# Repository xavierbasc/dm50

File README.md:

# DM50 calculator

The main features of the calculator are the following:

 - 32bit ARM Cortex-M33 MCU ultra low power.
 - Mathematical coprocessor acceleration.
 - Floating Point Unit (FPU).
 - 2MB RAM (STM32U595RJ).
 - 4MB FLASH memory (STM32U595RJ).
 - 16MB FLASH storage Octo-SPI (accessible via USB).
 - USBC port, connects as USB mass storage device.
 - Serial port for communications with external devices.
 - MicroSD memory slot.
 - Integrated speaker and stereo audio output (jack 3.5).
 - Graphic LCD Display (128x64 dots).
 - ESD protection of USBC.
 - LiPO 3.7V rechargeable battery, with JST PH2.0 connector.
 - Possibility of using AAA batteries.
 - Battery charge level sensor.
 - USB power and battery charging status LED indicators.
 - JTAG debug port.
 - Temperature sensor.
 - Same number of keys as the legendary HP48.

# Hardware
Below is a list of the most relevant electronic components:

1. Processor: STM32U5 ARM Cortex-M33 ultra low power with FPU.
2. Display: EA_DOGL128L-6 STN reflective display 128x64.
3. Flash memory: W25Q128JVSIQ 16MB Flash.
4. Voltage regulator: ADP2108 Vin 2.3 - 5.5, Vout 3.3.
5. USB protection: USBLC6-2 ESD protection of VBUS.
6. Battery charger: MCP73831 Lithium-Ion/Lithium-Polymer Battery Charger.

Some of the supported batteries are as follows:

| Batteries | Capacity (mha) |
| --- | :---: |
| AAA Alkaline | 900 - 1155 |
| AAA Ni-MH | 800 - 1000 |
| LiPO 402025 (4.0x20x25) | 150 |
| LiPO LP272247 (2.7x22x47) | 260 |

***Electronic design***:

## Case
Freecad software has been used to design the casing.
The spaces have been optimized to reduce the size, continuously giving shape to the calculator and improving the user experience.

## Faceplate
A master faceplate has been designed although it can be exchanged by the user through a simple manual process.

The front plate is printed on photographic paper and cut to size, with professional results. A photo-quality printer is recommended, such as the Epson Ecotank.

To create the faceplate, the Inkscape tool has been used to edit the SVG and the font used is Latin Modern Math, licensed by the GUST Font License, developed by the TeX user group in Poland, and can be used for academic use. , commercial or academic.

[Latin Modern Math font](https://www.gust.org.pl/projects/e-foundry/latin-modern "Latin Modern Math font")

# Software
TBD

# Reference
Comparison of the ***hardware*** used in the different reference calculators:

| Year | Model | Processor | FREQ | RAM | FLASH | Display | MIPS |
| :-: | - | - | -: | -: | -: | :-: | -: |
| 1988 | [HP42S](https://en.wikipedia.org/wiki/HP-42S) | HP Saturn (1LF5) | - | 8KB | 64KB | 131×16 | 0.5 |
| 1993 | [HP48G](https://en.wikipedia.org/wiki/HP_48_series) | HP Saturn (1LF2) | 4MHz | 32KB | 512KB | 131×64 | 0.5 |
| 2006 | [HP50G](https://en.wikipedia.org/wiki/HP_49/50_series) | ARM9 S3C2410 | 75MHz | 512KB | 2MB | 131×80 | 75 |
| 2013 | [TI-Nspire CX II](https://en.wikipedia.org/wiki/TI-Nspire_series#TI-Nspire_CX_II_and_TI-Nspire_CX_II_CAS) | TI OMAP 3530 | 396MHz | 64MB | 128MB | 320x240 | 792 |
| 2016 | [NumWorks](https://www.numworks.com/resources/engineering/hardware/) | STM32F730V8T6 | 216MHz | 256KB | 6MB | 320x240 | 432 |
| 2017 | [DM42](https://www.swissmicros.com/product/dm42) | STM32L476RG | 80MHz | 128KB | 6MB | 400×240 |  100 |
| 2019 | [HP Prime G2](https://en.wikipedia.org/wiki/HP_Prime) | i. MX 6ULL | 528MHz | 256MB | 512MB | 320×240 | 1710 |
| 2021 | [OpenRPNCalc](https://github.com/apoluekt/OpenRPNCalc) | STM32L476 | 8MHz | 128KB | 1MB | 400x240 | 100 |
| 2023 | [DM32](https://www.swissmicros.com/product/dm42) | STM32U575 | 160MHz | 786KB | 1MB | 400×240 |  240 |
| 2024 | [`DM50`](https://github.com/xavierbasc/dm50-calculator) | STM32U595RJ | 160MHz | 2MB | 20MB | 128×64 | 240 |

List of ***software*** used as firmware in some calculators:

1. [DB48X](https://48calc.org/): DB48X is a modern implementation of RPL.
2. [C47](https://47calc.com/): C47 is a RPN Scientific Calculator (old WP43C project).
3. [WP43](https://gitlab.com/rpncalculators/wp43): Firmware for the WP43 pocket calculator (old WP43S project).
4. [Free42](https://github.com/thomasokken/free42): Free42 is a software clone of the Hewlett-Packard 42S calculator.
5. [TCalc](https://github.com/tylertian123/TCalc): Firmware for STM32 CAS calculator.
6. [TinyExpr](https://github.com/codeplea/tinyexpr): parser and evaluation for math expressions.
7. [Giac](https://www-fourier.ujf-grenoble.fr/~parisse/giac.html): CAS calculation engine used in HP Prime, Casio Graph 90, Casio 35eii, TI Nspire CX, Numworks, and software such as Geogebra and PocketCAS.

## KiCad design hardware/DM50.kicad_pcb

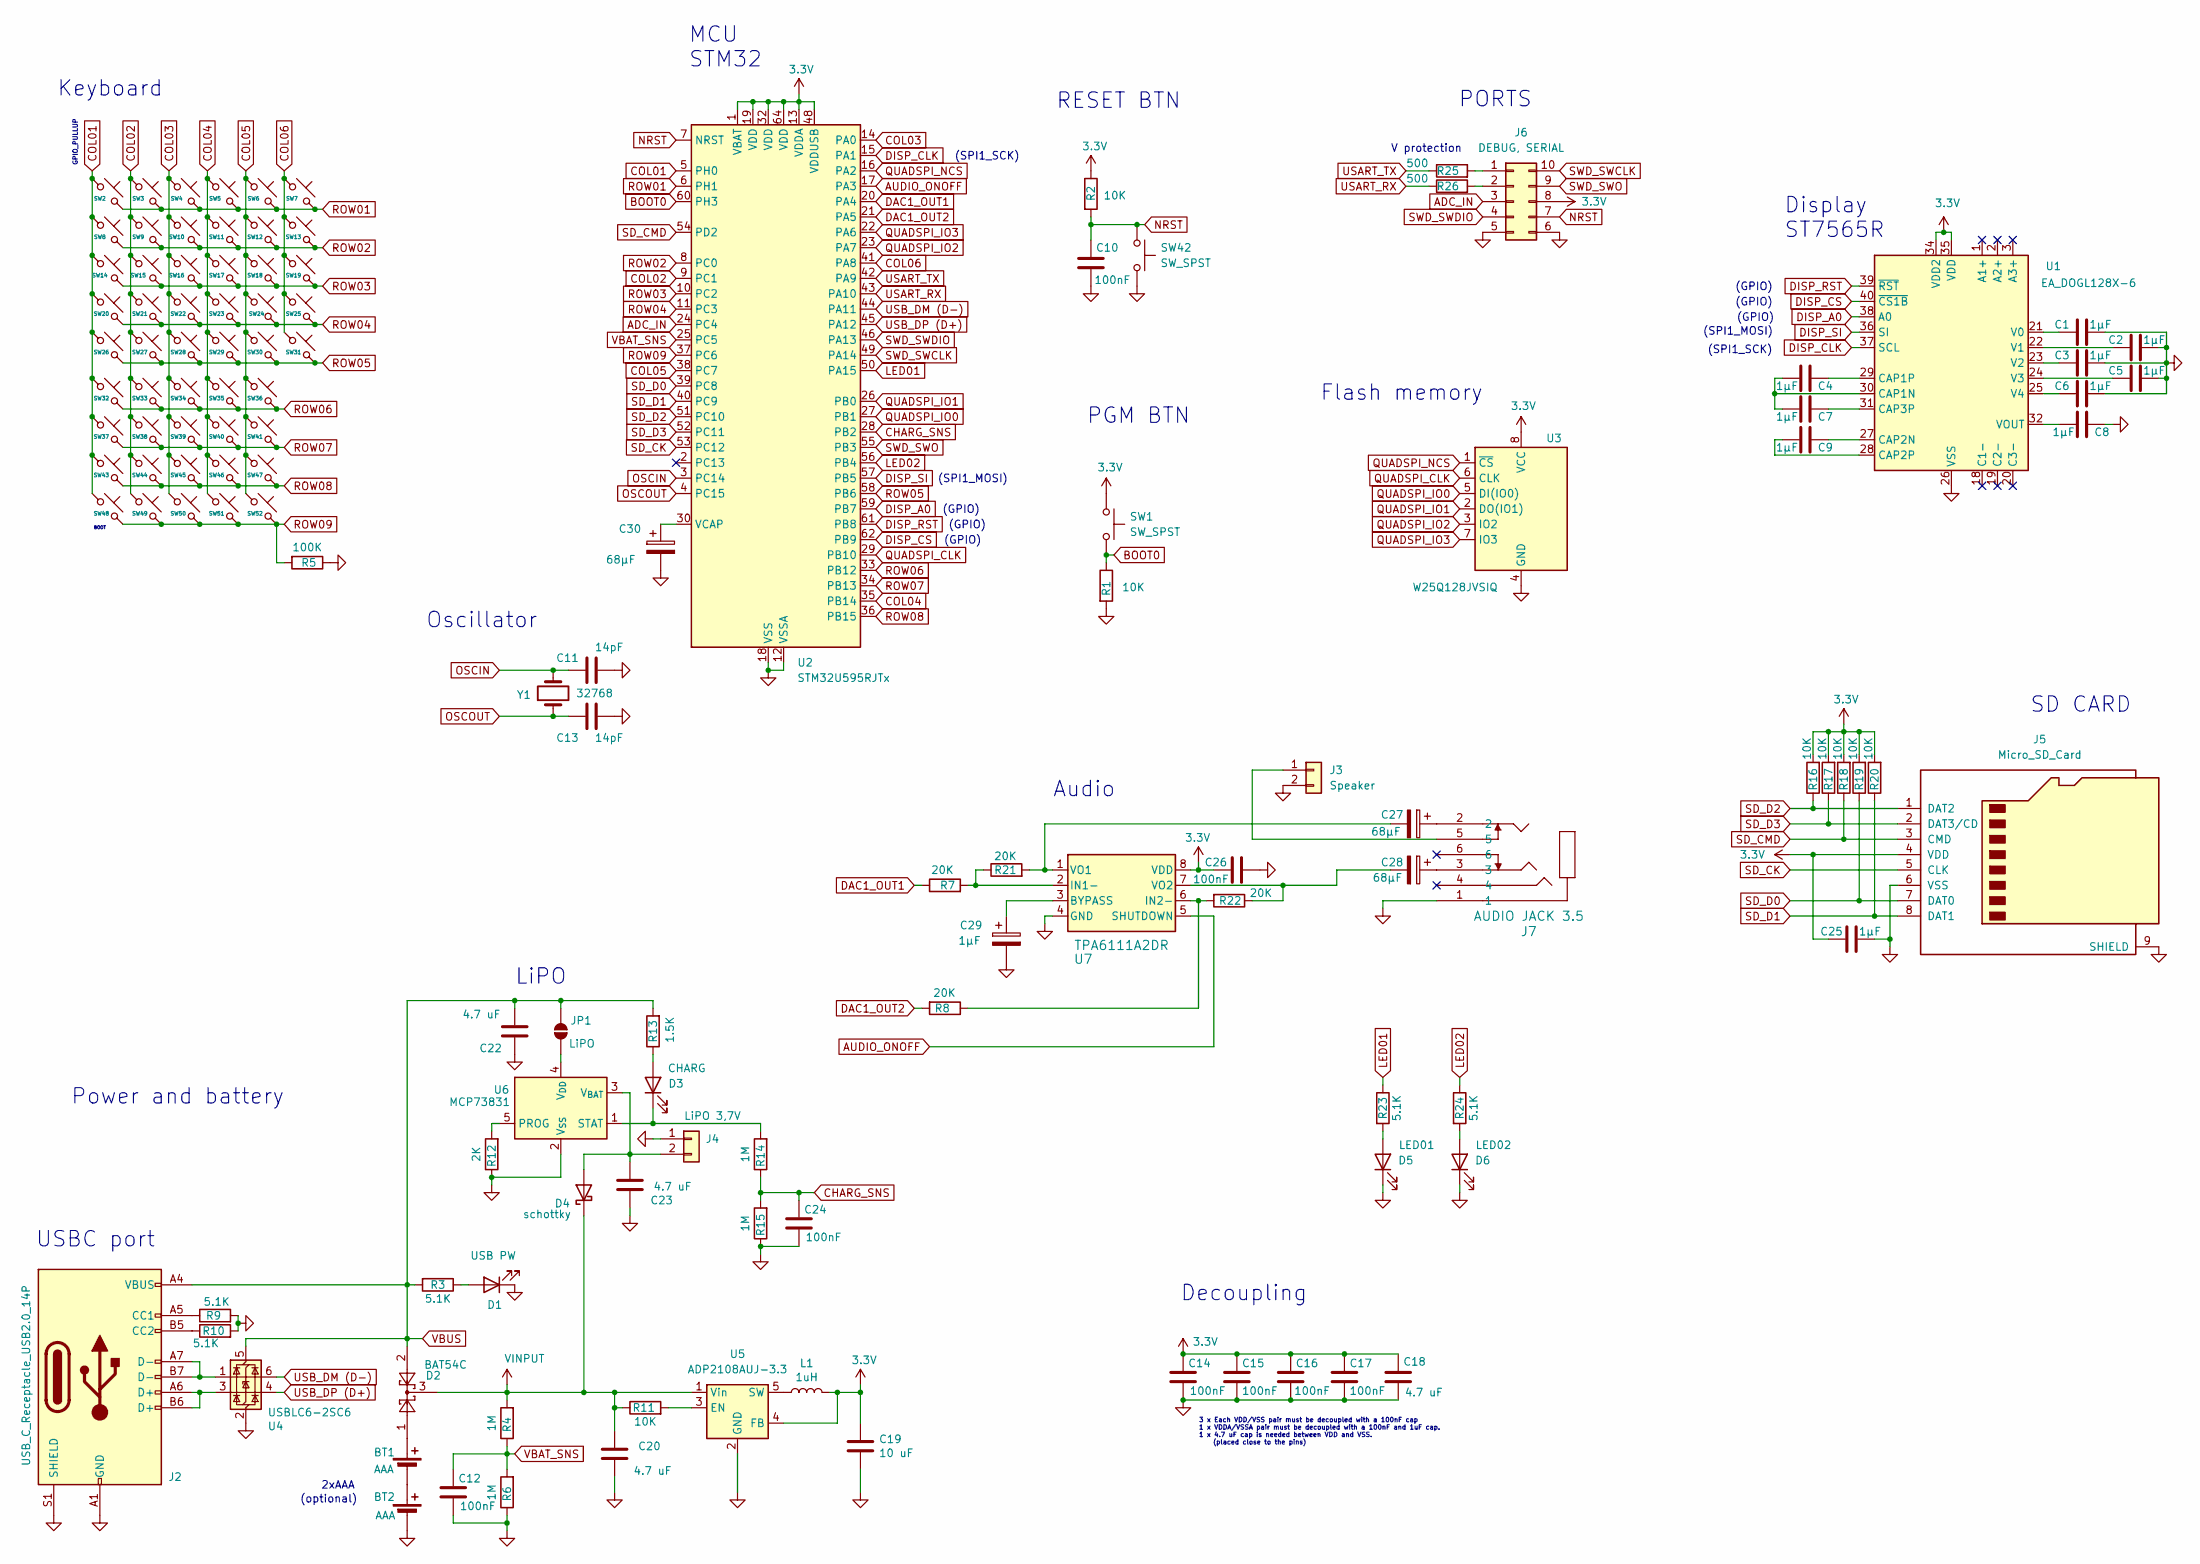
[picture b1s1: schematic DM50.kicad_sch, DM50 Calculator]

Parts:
BT1, BT2: AAA; dm50-batAAA; Digikey BK-82 (x4)
C1, C2, C3, C4, C5, C6, C7, C8, C9, C25, C29: 1µF; C_0603_1608Metric; Digikey CC0603KRX7R7BB105
C10, C12, C14, C15, C16, C17, C24, C26: 100nF; C_0603_1608Metric; Digikey CC0603KRX7R7BB104
C11, C13: 14pF; C_0603_1608Metric; Digikey CL10C060DB8NNNC
C18, C20, C22, C23: 4.7 uF; C_0603_1608Metric; Digikey CL10A475KP8NNNC
C19: 10 uF; C_0603_1608Metric; Digikey LMK107BBJ106MALT
C27, C28, C30: 68µF; C_1210_3225Metric; Digikey C3216X5R0J686M160AB
D1: USB PW; LED_0603_1608Metric; Digikey LTST-C190GKT
D2: BAT54C; SOT-23; Digikey BAT54C
D3: CHARG; LED_0603_1608Metric; Digikey LTST-S270KRKT
D4: schottky; D_SOD-323; Digikey 1PS76SB10,115
D5: LED01; LED_0603_1608Metric; Digikey LTST-S270KRKT
D6: LED02; LED_0603_1608Metric; Digikey LTST-S270KRKT
J2: USB_C_Receptacle_USB2.0_14P; USB_C_Receptacle_GCT_USB4105-xx-A_16P_TopMnt_Horizontal; Digikey 12402012E212A
J3: Speaker; Buzzer; Digikey CMS-15113-078L100
J4: LiPO 3,7V; CONN_S2B-PH-K-S_JST; Digikey S2B-PH-K-S
J5: Micro_SD_Card; 502570-0893_MOL; Digikey DM3AT-SF-PEJM5
J6: DEBUG, SERIAL; 610110249221; Digikey 610110249221
J7: AUDIO JACK 3.5; SJ-43516-SMT_CUD; Digikey SJ-43516-SMT-TR
JP1: LiPO; SolderJumper-2_P1.3mm_Bridged_RoundedPad1.0x1.5mm
L1: 1uH; L_0805_2012Metric_Pad1.15x1.40mm_HandSolder; Digikey MLZ1608A1R0WT000
R1, R2, R11, R16, R17, R18, R19, R20: 10K; R_0603_1608Metric; Digikey RMCF0603JT10K0
R3, R9, R10, R23, R24: 5.1K; R_0603_1608Metric; Digikey RC0603FR-075K1L
R4, R6, R14, R15: 1M; R_0603_1608Metric; Digikey RMCF0603FT1M00
R5: 100K; R_0603_1608Metric; Digikey RC0603FR-07100KL
R7, R8, R21, R22: 20K; R_0603_1608Metric; Digikey RMCF0603JT10K0
R12: 2K; R_0603_1608Metric; Digikey ERJ-3EKF2001V
R13: 1.5K; R_0603_1608Metric; Digikey RC0603JR-071K5L
R25, R26: 500; R_0603_1608Metric; Digikey RMCF0603JT10K0
SW1, SW42: SW_SPST; SW_SPST_CK_KMS2xxG; Digikey KMS223GPLFG
SW2, SW3, SW4, SW5, SW6, SW7, SW8, SW9, SW10, SW11, SW12, SW13, SW14, SW15, SW16, SW17, SW18, SW19, SW20, SW21, SW22, SW23, SW24, SW25, SW26, SW27, SW28, SW29, SW30, SW31, SW32, SW33, SW34, SW35, SW36, SW37, SW38, SW39, SW40, SW41, SW43, SW44, SW45, SW46, SW47, SW48, SW49, SW50, SW51, SW52: BT_SMD; dm50-button; Digikey dome 7.0mm, three dimple
U1: EA_DOGL128X-6; EA DOGL128L-6; Digikey EA DOGL128L-6
U2: STM32U595RJTx; LQFP-64_10x10mm_P0.5mm; Digikey STM32U595RJTx
U3: W25Q128JVSIQ; SOIC-8_3.9x4.9mm_P1.27mm; Digikey W25Q128JVSIQ
U4: USBLC6-2SC6; SOT-23-6; Digikey USBLC6-2SC6
U5: ADP2108AUJ-3.3; TSOT-23-5; Digikey ADP2108AUJZ-3.3-R7
U6: MCP73831; SOT-23-5; Digikey MCP73831T-2ACI/OT
U7: TPA6111A2DR; SOIC-8-1EP_3.9x4.9mm_P1.27mm_EP2.41x3.81mm_ThermalVias; Digikey TPA6111A2DR
Y1: 32768; XTAL_ABS05-32.768KHZ-9-T

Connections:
3.3V: C14.1, C15.1, C16.1, C17.1, C18.1, C19.1, C25.1, C26.1, J5.4 (VDD), J6.8, L1.2, R2.1, R16.2, R17.2, R18.2, R19.2, R20.2, SW1.1, U1.34 (VDD2), U1.35 (VDD), U2.1 (VBAT), U2.13 (VDDA), U2.19 (VDD), U2.32 (VDD), U2.48 (VDDUSB), U2.64 (VDD), U3.8 (VCC), U5.4 (FB), U7.8 (VDD)
ADC_IN: J6.3, U2.24 (PC4)
AUDIO_ONOFF: U2.17 (PA3), U7.5 (SHUTDOWN)
BOOT0: R1.1, SW1.2, U2.60 (PH3)
CHARG_SNS: C24.1, R14.1, R15.2, U2.28 (PB2)
COL01: SW2.1, SW8.1, SW14.1, SW20.1, SW26.1, SW32.1, SW37.1, SW43.1, SW48.1, U2.5 (PH0)
COL02: SW3.1, SW9.1, SW15.1, SW21.1, SW27.1, SW33.1, SW38.1, SW44.1, SW49.1, U2.9 (PC1)
COL03: SW4.1, SW10.1, SW16.1, SW22.1, SW28.1, SW34.1, SW39.1, SW45.1, SW50.1, U2.14 (PA0)
COL04: SW5.1, SW11.1, SW17.1, SW23.1, SW29.1, SW35.1, SW40.1, SW46.1, SW51.1, U2.35 (PB14)
COL05: SW6.1, SW12.1, SW18.1, SW24.1, SW30.1, SW36.1, SW41.1, SW47.1, SW52.1, U2.38 (PC7)
COL06: SW7.1, SW13.1, SW19.1, SW25.1, SW31.1, U2.41 (PA8)
DAC1_OUT1: R7.1, U2.20 (PA4)
DAC1_OUT2: R8.2, U2.21 (PA5)
DISP_A0: U1.38 (A0), U2.59 (PB7)
DISP_CLK: U1.37 (SCL), U2.15 (PA1)
DISP_CS: U1.40 (~CS1B), U2.62 (PB9)
DISP_RST: U1.39 (~RST), U2.61 (PB8)
DISP_SI: U1.36 (SI), U2.57 (PB5)
GND: BT2.2 (-), C1.2, C2.2, C3.2, C5.2, C6.2, C8.1, C10.2, C11.2, C12.2, C13.2, C14.2, C15.2, C16.2, C17.2, C18.2, C19.2, C20.2, C22.1, C23.2, C24.2, C25.2, C26.2, C29.2, C30.2, D1.1 (K), D5.1 (K), D6.1 (K), J2.A1 (GND), J2.A12 (GND), J2.B1 (GND), J2.B12 (GND), J2.S1 (SHIELD), J3.2, J4.1, J5.6 (VSS), J5.9 (SHIELD), J6.5, J6.6, J7.1, R1.2, R5.1, R6.1, R9.2, R10.2, R12.1, R15.1, SW42.2, U1.26 (VSS), U1.33 (VSS), U2.12 (VSSA), U2.18 (VSS), U2.31 (VSS), U2.47 (VSS), U2.63 (VSS), U3.4 (GND), U4.2 (GND), U5.2 (GND), U6.2 (V_{SS}), U7.4 (GND)
LED01: R23.1, U2.50 (PA15)
LED02: R24.1, U2.56 (PB4)
NRST: C10.1, J6.7, R2.2, SW42.1, U2.7 (NRST)
unnamed: BT1.1 (+), D2.1
unnamed: BT1.2 (-), BT2.1 (+)
unnamed: C27.1, J7.2
unnamed: C28.1, J7.3
unnamed: D1.2 (A), R3.1
unnamed: D3.2 (A), R13.1
unnamed: D3.1 (K), R14.2, U6.1 (STAT)
unnamed: C23.1, D4.2 (A), J4.2, U6.3 (V_{BAT})
unnamed: D5.2 (A), R23.2
unnamed: D6.2 (A), R24.2
unnamed: J2.A5 (CC1), R9.1
unnamed: J2.B5 (CC2), R10.1
unnamed: J2.A6 (D+), J2.B6 (D+), U4.3 (I/O2)
unnamed: J2.A7 (D-), J2.B7 (D-), U4.1 (I/O1)
unnamed: J3.1, J7.5
unnamed: J6.1, R25.2
unnamed: J6.2, R26.2
unnamed: JP1.1 (A), U6.4 (V_{DD})
unnamed: C4.2, C7.2, U1.30 (CAP1N)
unnamed: C4.1, U1.29 (CAP1P)
unnamed: C9.1, U1.27 (CAP2N)
unnamed: C9.2, U1.28 (CAP2P)
unnamed: C7.1, U1.31 (CAP3P)
unnamed: C1.1, U1.21 (V0)
unnamed: C2.1, U1.22 (V1)
unnamed: C3.1, U1.23 (V2)
unnamed: C5.1, U1.24 (V3)
unnamed: C6.1, U1.25 (V4)
unnamed: C8.2, U1.32 (VOUT)
unnamed: C30.1, U2.30 (VCAP)
unnamed: R11.2, U5.3 (EN)
unnamed: L1.1, U5.5 (SW)
unnamed: R12.2, U6.5 (PROG)
unnamed: C29.1, U7.3 (BYPASS)
unnamed: R7.2, R21.1, U7.2 (IN1-)
unnamed: R8.1, R22.2, U7.6 (IN2-)
unnamed: C27.2, R21.2, U7.1 (VO1)
unnamed: C28.2, R22.1, U7.7 (VO2)
OSCIN: C11.1, U2.3 (PC14), Y1.2
OSCOUT: C13.1, U2.4 (PC15), Y1.1
QUADSPI_CLK: U2.29 (PB10), U3.6 (CLK)
QUADSPI_IO0: U2.27 (PB1), U3.5 (DI(IO0))
QUADSPI_IO1: U2.26 (PB0), U3.2 (DO(IO1))
QUADSPI_IO2: U2.23 (PA7), U3.3 (IO2)
QUADSPI_IO3: U2.22 (PA6), U3.7 (IO3)
QUADSPI_NCS: U2.16 (PA2), U3.1 (~CS)
ROW01: SW2.2, SW3.2, SW4.2, SW5.2, SW6.2, SW7.2, U2.6 (PH1)
ROW02: SW8.2, SW9.2, SW10.2, SW11.2, SW12.2, SW13.2, U2.8 (PC0)
ROW03: SW14.2, SW15.2, SW16.2, SW17.2, SW18.2, SW19.2, U2.10 (PC2)
ROW04: SW20.2, SW21.2, SW22.2, SW23.2, SW24.2, SW25.2, U2.11 (PC3)
ROW05: SW26.2, SW27.2, SW28.2, SW29.2, SW30.2, SW31.2, U2.58 (PB6)
ROW06: SW32.2, SW33.2, SW34.2, SW35.2, SW36.2, U2.33 (PB12)
ROW07: SW37.2, SW38.2, SW39.2, SW40.2, SW41.2, U2.34 (PB13)
ROW08: SW43.2, SW44.2, SW45.2, SW46.2, SW47.2, U2.36 (PB15)
ROW09: R5.2, SW48.2, SW49.2, SW50.2, SW51.2, SW52.2, U2.37 (PC6)
SD_CK: J5.5 (CLK), U2.53 (PC12)
SD_CMD: J5.3 (CMD), R18.1, U2.54 (PD2)
SD_D0: J5.7 (DAT0), R19.1, U2.39 (PC8)
SD_D1: J5.8 (DAT1), R20.1, U2.40 (PC9)
SD_D2: J5.1 (DAT2), R16.1, U2.51 (PC10)
SD_D3: J5.2 (DAT3/CD), R17.1, U2.52 (PC11)
SWD_SWCLK: J6.10, U2.49 (PA14)
SWD_SWDIO: J6.4, U2.46 (PA13)
SWD_SWO: J6.9, U2.55 (PB3)
USART_RX: R26.1, U2.43 (PA10)
USART_TX: R25.1, U2.42 (PA9)
USB_DM (D-): U2.44 (PA11), U4.6 (I/O1)
USB_DP (D+): U2.45 (PA12), U4.4 (I/O2)
VBAT_SNS: C12.1, R4.1, R6.2, U2.25 (PC5)
VBUS: C22.2, D2.2, J2.A4 (VBUS), J2.A9 (VBUS), J2.B4 (VBUS), J2.B9 (VBUS), JP1.2 (B), R3.2, R13.2, U4.5 (VBUS)
VINPUT: C20.1, D2.3, D4.1 (K), R4.2, R11.1, U5.1 (Vin)

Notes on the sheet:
(GPIO)
Oscillator
(optional)
Decoupling
(SPI1_MOSI)
PORTS
Power and battery
MCU STM32
USBC port
V protection
Keyboard
GPIO_PULLUP
Flash memory
2xAAA
LiPO
Display ST7565R
(SPI1_SCK)
PGM BTN
SD CARD
RESET BTN
3 x Each VDD/VSS pair must be decoupled with a 100nF cap 1 x VDDA/VSSA pair must be decoupled with a 100nF and 1uF cap. 1 x 4.7 uF cap is needed between VDD and VSS. (placed close to the pins)
Audio
BOOT

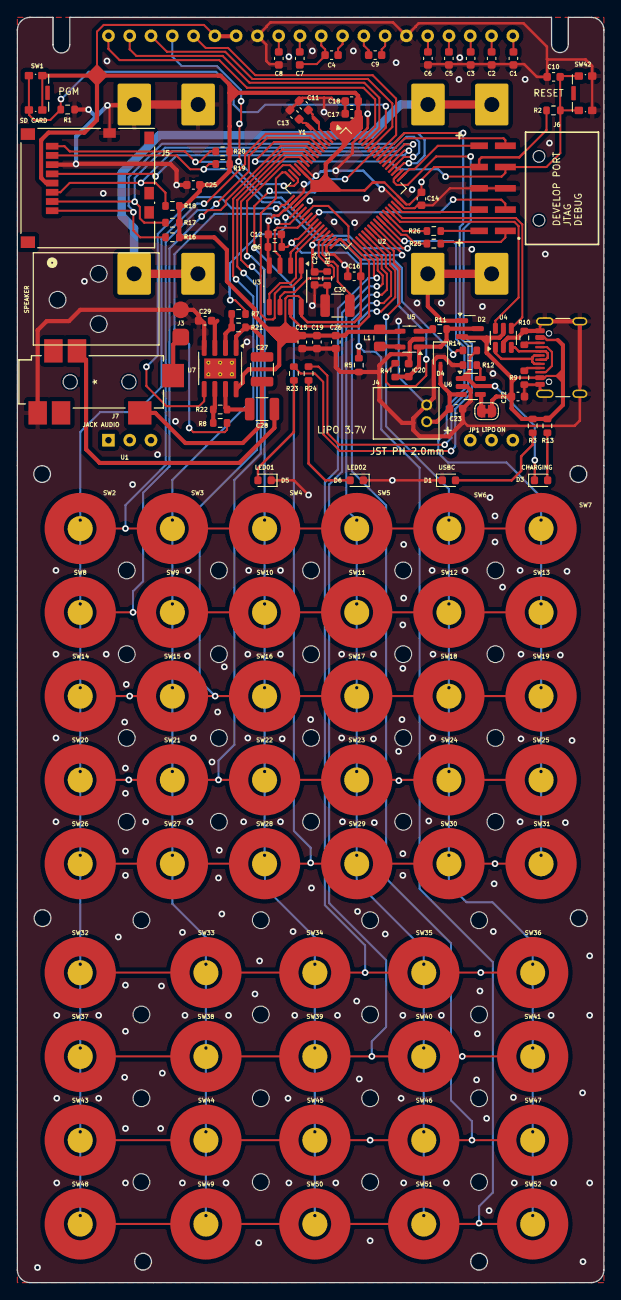
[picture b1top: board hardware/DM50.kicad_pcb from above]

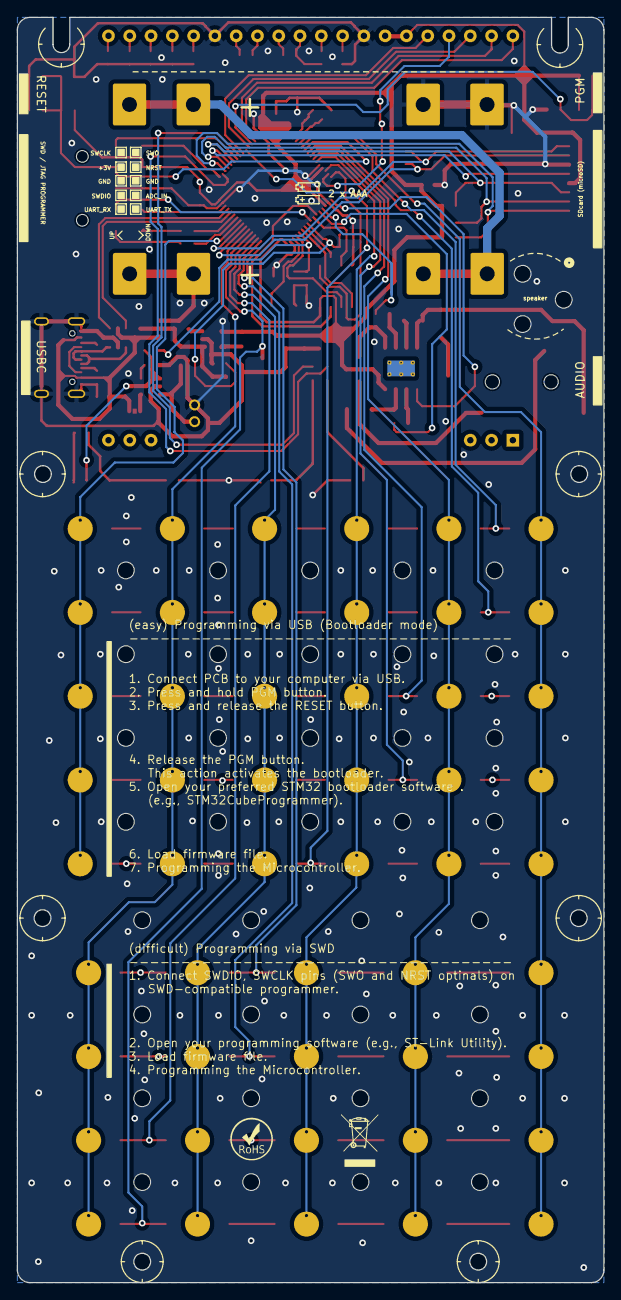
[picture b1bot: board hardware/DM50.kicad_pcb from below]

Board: 2 copper layers, 70.0 x 151.0 mm, 131 parts (2 on the bottom side), 93 nets.

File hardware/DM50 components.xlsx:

Reference | Value | Datasheet | Footprint | Qty | Digikey | Package | Price € | TOTAL | Function |  | BASIC (AAA) | PRO (LiPO+microSD)
C1,C2,C3,C4,C5,C6,C7,C8,C9,C25 | 1uF | https://www.digikey.es/en/products/detail/yageo/CC0603KRX7R7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 | Capacitor_SMD:C_0603_1608Metric | 10 | CC0603KRX7R7BB105 | 0603 | 0.09 | 0.89999999999999991 | Core | UNION 1uF (A8) | 0.89999999999999991 | 0.89999999999999991
C10,C12,C14,C15,C16,C17,C24,C26 | 100nF | https://www.digikey.es/es/products/detail/yageo/CC0603KRX7R7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 | Capacitor_SMD:C_0603_1608Metric | 8 | CC0603KRX7R7BB104 | 0603 | 0.09 | 0.72 | Core |  | 0.72 | 0.72
C11,C13 | 6pF | https://www.digikey.es/es/products/detail/samsung-electro-me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 | Capacitor_SMD:C_0603_1608Metric | 2 | CL10C060DB8NNNC | 0603 | 0.09 | 0.18 | Core |  | 0.18 | 0.18
C18,C20,C22,C23 | 4.7 uF | https://www.digikey.es/es/products/detail/samsung-electro-me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 | Capacitor_SMD:C_0603_1608Metric | 4 | CL10A475KP8NNNC | 0603 | 0.09 | 0.36 | Core |  | 0.36 | 0.36
C19 | 10 uF | https://www.digikey.es/es/products/detail/taiyo-yuden/LMK107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 | Capacitor_SMD:C_0603_1608Metric | 1 | LMK107BBJ106MALT | 0603 | 0.14000000000000001 | 0.14000000000000001 | Core |  | 0.14000000000000001 | 0.14000000000000001
C27,C28,C30 | 68µF | https://www.digikey.es/es/products/detail/tdk-corporation/C3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 |  | 3 | C3216X5R0J686M160AB | 1206 | 0.49 | 1.47 | AUDIO (2/3) | MODIFICADO | 0.49 | 1.47
C29 | 1µF | https://www.digikey.es/es/products/detail/yageo/CC0603KRX7R7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 | Capacitor_SMD:C_1206_3216Metric | 1 | CC0603KRX7R7BB105 | 0603 | 0.09 | 0.09 | Core |  | 0.09 | 0.09
D1 | GREEN LED | https://www.digikey.es/es/products/detail/liteon/LTST-C190GK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 | LED_SMD:LED_0603_1608Metric | 1 | LTST-C190GKT | 0603 | 0.19 | 0.19 | Core |  |  | 0.19
D2 | BAT54C | https://www.digikey.es/es/products/detail/evvo/BAT54C/21407177 | Package_TO_SOT_SMD:SOT-23 | 1 | BAT54C | SOT-23 | 0.1 | 0.1 | Core |  | 0.1 | 0.1
D3 | RED LED | https://www.digikey.es/es/products/detail/liteon/LTST-S270KR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 | LED_SMD:LED_0603_1608Metric | 1 | LTST-S270KRKT | 0603 | 0.19 | 0.19 | Core |  | 0.19 | 0.19
D4 | schottky | https://www.digikey.es/es/products/detail/nexperia-usa-inc/1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 | Diode_SMD:D_SOD-323 | 1 | 1PS76SB10,115 | SOD-323 | 0.17 | 0.17 | Core |  |  | 0.17
J2 | USB_C_Receptacle_USB2.0_14P | https://www.digikey.es/es/products/detail/amphenol-cs-commer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 | Connector_USB:USB_C_Receptacle_GCT_USB4105-xx-A_16P_TopMnt_Horizontal | 1 | 12402012E212A | USBC 24p | 0.76 | 0.76 | Core |  | 0.76 | 0.76
J3 | Speaker | https://www.digikey.es/es/products/detail/cui-devices/CMS-15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 | DM50:Buzzer | 1 | CMS-15113-078L100 | 15x11x3 mm | 1.39 | 1.39 | AUDIO |  |  | 1.39
J4 | LiPO 3,7V | https://www.digikey.es/es/products/detail/jst-sales-america-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 | DM50:CONN_S2B-PH-K-S_JST | 1 | S2B-PH-K-S | S2B-PH-K | 0.11 | 0.11 | LIPO |  |  | 0.11
J5 | Micro_SD_Card | https://www.digikey.es/es/products/detail/gct/MEM2075-00-140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 |  | 1 | MEM2075-00-140-01-A | MEM2075 | 1.78 | 1.78 | MICROSD | MODIFICADO |  | 1.78
J6 | DEBUG, SERIAL | https://www.digikey.es/es/products/detail/w%C3%BCrth-elektro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 | DM50:610110249221 | 1 | 610110249221 | CONN 2x10 | 1.94 | 1.94 | DEBUG-SERIAL | MODIFICADO |  | 1.94
J7 | SJ-43516-SMT-TR | https://www.digikey.es/es/products/detail/cui-devices/SJ-435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 | DM50:SJ-43516-SMT_CUD | 1 | SJ-43516-SMT-TR | CONN JACK 3.5 | 0.94 | 0.94 | AUDIO |  |  | 0.94
L1 | 1uH | https://www.digikey.es/es/products/detail/tdk-corporation/ML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 | Inductor_SMD:L_0805_2012Metric_Pad1.15x1.40mm_HandSolder | 1 | MLZ1608A1R0WT000 | 0603 | 0.13 | 0.13 | Core |  | 0.13 | 0.13
R1,R2,R11,R16,R17,R18,R19,R20 | 10K | https://www.digikey.es/es/products/detail/stackpole-electron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 | Resistor_SMD:R_0603_1608Metric | 8 | RMCF0603JT10K0 | 0603 | 0.09 | 0.72 | Core |  | 0.72 | 0.72
R3,R9,R10 | 5.1K | https://www.digikey.es/es/products/detail/yageo/RC0603FR-075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 | Resistor_SMD:R_0603_1608Metric | 3 | RC0603FR-075K1L | 0603 | 0.09 | 0.27 | Core |  | 0.27 | 0.27
R4,R6,R14,R15 | 1M | https://www.digikey.es/es/products/detail/stackpole-electron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 | Resistor_SMD:R_0603_1608Metric | 4 | RMCF0603FT1M00 | 0603 | 0.09 | 0.36 | Core |  | 0.36 | 0.36
R5 | 100K | https://www.digikey.es/es/products/detail/yageo/RC0603FR-071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 | Resistor_SMD:R_0603_1608Metric | 1 | RC0603FR-07100KL | 0603 | 0.09 | 0.09 | Core |  | 0.09 | 0.09
R7,R8,R21,R22 | 20K | https://www.digikey.es/es/products/detail/stackpole-electron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 | Resistor_SMD:R_0603_1608Metric | 4 | RMCF0603JT10K0 | 0603 | 0.09 | 0.36 | Core |  | 0.36 | 0.36
R12 | 2K | https://www.digikey.es/es/products/detail/panasonic-electron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 | Resistor_SMD:R_0603_1608Metric | 1 | ERJ-3EKF2001V | 0603 | 0.09 | 0.09 | Core |  | 0.09 | 0.09
R13 | 1.5K | https://www.digikey.es/es/products/detail/yageo/RC0603JR-071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 | Resistor_SMD:R_0603_1608Metric | 1 | RC0603JR-071K5L | 0603 | 0.09 | 0.09 | Core |  | 0.09 | 0.09
SW1,SW42 | SW_SPST | https://www.digikey.es/es/products/detail/c-k/PTS526-SK15-SM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 | Button_Switch_SMD:SW_SPST_CK_KMS2xxG | 2 | KMS223GPLFG | KMS223 | 0.61 | 1.22 | Core |  | 1.22 | 1.22
SW2,SW3,SW4,SW5,SW6,SW7,SW8,SW9,SW10,SW11,SW12,SW13,SW14,SW15,SW16,SW17,SW18,SW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 | BT_SMD | https://es.aliexpress.com/item/1005001444483167.html?srcSns=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 | DM50:dm50-button | 50 |  | dome 7.0mm, three dimple | 0.02 | 1 | Core |  | 1 | 1
U1 | EA_DOGL128X-6 | https://www.digikey.es/es/products/detail/display-visions/EA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 | DM50:EA_DOGL128-6 | 1 | EA DOGL128L-6 | EA DOGL128L-6 | 11.22 | 11.22 | Core |  | 11.22 | 11.22
U2 | STM32U595RJTx | https://www.st.com/resource/en/datasheet/stm32u595rj.pdf | Package_QFP:LQFP-64_10x10mm_P0.5mm | 1 | STM32U595RJTx | LQFP64 | 13.7 | 13.7 | Core |  | 13.7 | 13.7
U3 | W25Q128JVSIQ | https://www.digikey.es/es/products/detail/winbond-electronic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 | Package_SO:SOIC-8_3.9x4.9mm_P1.27mm | 1 | W25Q128JVSIQ | 8-SOIC | 1.55 | 1.55 | Core |  | 1.55 | 1.55
U4 | USBLC6-2SC6 | https://www.digikey.es/es/products/detail/stmicroelectronics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 | Package_TO_SOT_SMD:SOT-23-6 | 1 | USBLC6-2SC6 | SOT-23-6 | 0.31 | 0.31 | Core |  | 0.31 | 0.31
U5 | ADP2108AUJ-3.3 | https://www.digikey.es/es/products/detail/analog-devices-inc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 | Package_TO_SOT_SMD:TSOT-23-5 | 1 | ADP2108AUJZ-3.3-R7 | TSOT-23-5 | 3.13 | 3.13 | Core | MODIFICAR | 3.13 | 3.13
U6 | MCP73831 | https://www.digikey.es/es/products/detail/microchip-technolo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 | Package_TO_SOT_SMD:SOT-23-5 | 1 | MCP73831T-2ACI/OT | SOT-23-5 | 0.68 | 0.68 | LIPO |  |  | 0.68
U7 | TPA6111A2DR | https://www.digikey.es/es/products/detail/texas-instruments/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 | Package_SO:SOIC-8-1EP_3.9x4.9mm_P1.27mm_EP2.41x3.81mm_ThermalVias | 1 | TPA6111A2DR | 8-SOIC | 0.76 | 0.76 | AUDIO |  |  | 0.76
Y1 | 32768 | https://www.digikey.es/es/products/detail/abracon-llc/ABS05-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 | DM50:XTAL_ABS05-32.768KHZ-9-T | 1 | ABS05-32.768KHZ-9-T | 1.6x1.0 | 0.78 | 0.78 | Core |  | 0.78 | 0.78
CONN AAA | CONN AAA | https://www.digikey.es/es/products/detail/mpd-memory-protect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 |  | 4 | BK-82 |  | 0.4 | 1.6 | AAA |  | 1.6
 |  |  |  |  |  |  |  |  |  |  |  | 0
PCB jlcpcb |  | https://jlcpcb.com | 33€ / 5 PCBs + SMT Stencil + shipping | 1 |  |  | 7 | 7 | PCB |  | 7 | 7
RESIN CASE |  | https://www.elegoo.com/products/abs-like-photopolymer-resin-v3 | 20€ / 1kg | 1 |  |  | 6 | 6 | CASE |  | 6 | 6
Screws |  | https://a.aliexpress.com/_EHVNaDX | 2€ / 100 pieces | 6 |  | M2 x 4mm | 0.02 | 0.12 |  |  | 0.12 | 0.12
Nuts |  | https://a.aliexpress.com/_EyaJlxR | 3€ / 50 pieces | 6 |  | M2 x 3mm | 0.06 | 0.36 |  |  | 0.36 | 0.36
LiPO |  | https://a.aliexpress.com/_Ez9zchP | 402025, 3,7 V, 150mAh | 1 |  | 20x25 | 4 | 4 | LIPO |  |  | 4
 |  |  |  |  |  |  |  | 47.889999999999993 | ELECTRONIC |  | 38.949999999999996 | 47.889999999999993
Superfluous not accounted: |  |  |  |  |  |  |  | 75.426900000000003 | TOTAL +IVA |  | 60.60949999999999 | 75.426900000000003
Adhesive paper for domes
Acrylic paints (Vallejo, etc)
Acrylic grip mix on plastics
Black EVA foam
Photo paper for bezel
CAMBIOS PROPUESTOS:
U6 | MCP1603T-330I/OS | https://www.digikey.es/es/products/detail/microchip-technolo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 |  | 1 |  | TSOT-23-5 | 1.19 | 1.19

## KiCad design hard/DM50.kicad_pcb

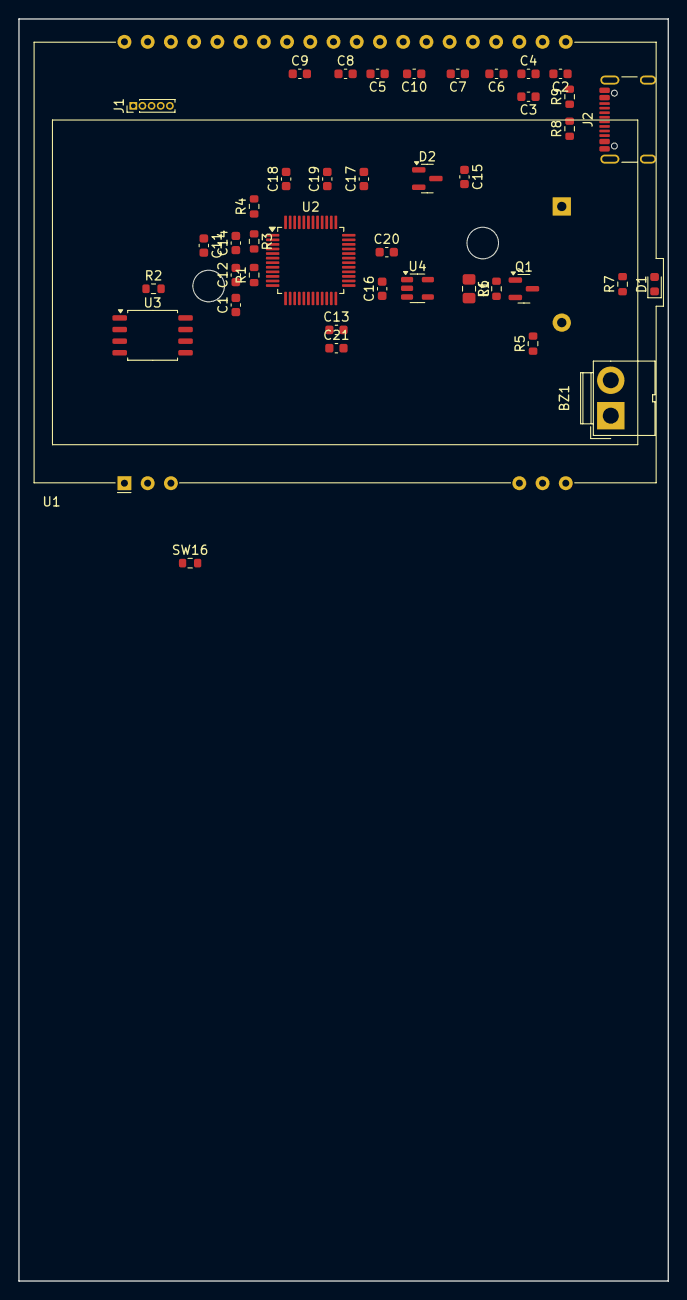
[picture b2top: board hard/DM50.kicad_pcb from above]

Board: 2 copper layers, 71.0 x 138.0 mm, 43 parts (1 on the bottom side), 47 nets, no tracks yet.

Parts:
BT1: 2xAAA (1.5V); BatteryHolder_Keystone_2468_2xAAA
BZ1: Buzzer; JWT_A3963_1x02_P3.96mm_Vertical
C1, C17, C18, C19, C20, C21: 100nF; C_0603_1608Metric
C2, C3, C4, C5, C6, C7, C8, C9, C10: 1uF; C_0603_1608Metric
C11, C12: 8pF; C_0603_1608Metric
C13: 2.2uF; C_0603_1608Metric
C14: 104; C_0603_1608Metric
C15: 4.7 uF; C_0603_1608Metric
C16: 10 uF; C_0603_1608Metric
D1: LED (RED); LED_0603_1608Metric
D2: BAT54C; SOT-23
J1: ST-LINK; PinHeader_1x05_P1.00mm_Vertical
J2: USB_C_Receptacle_USB2.0_14P; USB_C_Receptacle_GCT_USB4105-xx-A_16P_TopMnt_Horizontal
L1: 1uH; L_0805_2012Metric_Pad1.15x1.40mm_HandSolder
Q1: MMBT3904; SOT-23
R1: 10k; R_0603_1608Metric
R2: 4.7K; R_0603_1608Metric
R3, R4: 10K; R_0603_1608Metric
R5, R6: R; R_0603_1608Metric
R7, R8, R9: 5.1K; R_0603_1608Metric
SW16: R; R_0603_1608Metric
U1: EA_DOGL128X-6; EA_DOGL128-6
U2: STM32U535CBT6; LQFP-48_7x7mm_P0.5mm
U3: W25Q32JVSS; SOIC-8_5.23x5.23mm_P1.27mm
U4: ADP2108AUJ-3.3; TSOT-23-5

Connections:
3.3V: BZ1.1 (+), C16.1, C17.1, C18.1, C19.1, C20.1, C21.1, L1.2, R1.1, R2.2, R5.1, U1.34 (VDD2), U1.35 (VDD), U2.1 (VBAT), U2.9 (VDDA), U2.24 (VDD), U2.36 (VDD), U2.48 (VDD), U3.3 (IO2), U3.7 (IO3), U3.8 (VCC), U4.4 (FB)
/NRST: C1.1, J1.5, R1.2, U2.7 (NRST)
BUZZER: R6.1, U2.40 (PB4)
COL03: SW16.1, U2.30 (PA9)
DISP_A0: U1.38 (A0), U2.12 (PA2)
DISP_CS1B: U1.40 (~CS1B), U2.13 (PA3)
DISP_RST: U1.39 (~RST), U2.14 (PA4)
DISP_SCL: U1.37 (SCL), U2.10 (PA0)
DISP_SI: U1.36 (SI), U2.11 (PA1)
GND: BT1.2 (-), C1.2, C2.2, C3.2, C4.2, C6.2, C7.2, C9.1, C11.2, C12.2, C13.2, C14.1, C15.2, C16.2, C17.2, C18.2, C19.2, C20.2, C21.2, D1.1 (K), J1.1, J2.A1 (GND), J2.A12 (GND), J2.B1 (GND), J2.B12 (GND), J2.S1 (SHIELD), Q1.2 (E), R4.1, R8.2, R9.2, U1.26 (VSS), U1.33 (VSS), U2.8 (VSSA), U2.23 (VSS), U2.35 (VSS), U2.47 (VSS), U3.4 (GND), U4.2 (GND)
LED01: R7.1, U2.41 (PB5)
unnamed: BT1.1 (+), D2.1
unnamed: BZ1.2 (-), Q1.3 (C), R5.2
unnamed: D1.2 (A), R7.2
unnamed: D2.2, J2.A4 (VBUS), J2.A9 (VBUS), J2.B4 (VBUS), J2.B9 (VBUS)
unnamed: J2.A5 (CC1), R8.1
unnamed: J2.B5 (CC2), R9.1
unnamed: Q1.1 (B), R6.2
unnamed: R3.2, R4.2
unnamed: C5.2, C8.2, U1.30 (CAP1N)
unnamed: C5.1, U1.29 (CAP1P)
unnamed: C10.1, U1.27 (CAP2N)
unnamed: C10.2, U1.28 (CAP2P)
unnamed: C8.1, U1.31 (CAP3P)
unnamed: C2.1, U1.21 (V0)
unnamed: C3.1, U1.22 (V1)
unnamed: C4.1, U1.23 (V2)
unnamed: C6.1, U1.24 (V3)
unnamed: C7.1, U1.25 (V4)
unnamed: C9.2, U1.32 (VOUT)
unnamed: C11.1, U2.5 (PH0)
unnamed: C12.1, U2.6 (PH1)
unnamed: C13.1, U2.22 (VCAP)
unnamed: R2.1, U3.1 (~CS)
unnamed: L1.1, U4.5 (SW)
unnamed: C15.1, D2.3, U4.1 (Vin)
POWER_ON: U2.4 (PC15), U4.3 (EN)
ROW03: SW16.2, U2.46 (PB9)
SPI_MISO: U2.16 (PA6), U3.2 (DO(IO1))
SPI_MOSI: U2.17 (PA7), U3.5 (DI(IO0))
SPI_SCK: U2.15 (PA5), U3.6 (CLK)
SWCLK: J1.3, U2.37 (PA14)
SWDIO: J1.4, U2.34 (PA13)
SWO: J1.2, U2.39 (PB3)
USB_DM (D-): J2.A7 (D-), J2.B7 (D-), U2.32 (PA11)
USB_DP (D+): J2.A6 (D+), J2.B6 (D+), U2.33 (PA12)
WAKEUP01: C14.2, R3.1, U2.2 (PC13)
